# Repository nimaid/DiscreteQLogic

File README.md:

# DiscreteQLogic
My resources and projects relating to digital circuits made out of discrete transistors.

## Efficient Discrete NMOS Logic Gate Designs
I have yet to find a well-compiled source that lists the most efficient NMOS implementations using discrete MOSFETS and resistors. This is likely because, well, it's a very slow and outdated technology that draws more power than CMOS.

However, for DIY projects where one wishes to do the bare minimum of soldering, layout, and purchasing, NMOS provides very good functionality at about half the transistor count of CMOS (at the expense of adding some resistors). Therefore, I have decided to use NMOS for my DIY projects, and as such, I have been collecting the most efficient gate designs, which use fewest transistors and resistors possible.

*(I have been making a library of these parts for both Digital and LTspice, in order to simulate them before building them. You can find these libraries in their respective subfolders of this repository.)*

For this list, I will use some shorthand notation to refer to the total transistor and resistor counts for each part. This shorthand will follow the format `xQyR`, where `x` is the total transistor count and `y` is the total resistor count. So, for example, an XOR gate which was labeled `6Q3R` would require 6 transistors and 3 resistors to build.

Sometimes, you may see the part count listed in the format `(!aQbR/xQyR)`. This means the simplest (lowest part count) version of the part has it's input(s) or output(s) inverted (the `!` means `NOT` or inversion). *This inverted version uses `a` transistors and `b` resistors.* In order to use the part in it's non-inverted state, one or more NOT gates is needed, which increases the total component count per part. *This non-inverted version uses `x` transistors and `y` resistors.* If you are using many of these parts with a shared signal on their inputs (like a clock), it is more economical to invert that signal *once* before it then goes into each of the inverted variants of the part. In addition, sometimes you get inverted outputs for free (like with latches and flip-flops), so you actually don't even need NOT gates a lot of the time! This can save a *TON* of components when building things like multi-bit registers or enablers, where the savings add up with more bits.

Unless otherwise stated, all transistors are N-type.

Resistor values should be chosen based on acceptable power dissipation and speed requirements. If the resistors are large (on the order of 10kΩ+), then power dissipation will be very low (the resistor lets less current through to ground), but the response time of the gate will be much slower. This is due to an inherent weakness in NMOS where it takes longer to charge up the combined gate capacitance of the MOSFETs and the stray capacitance in the wires though a larger resistor. Conversely, smaller values will yield higher power usage, but faster response times.

### NOT (1Q1R)
<details>
<summary>Details</summary>

The simplest gate to construct is a NOT gate (also known as an inverter). This is simply a pullup resistor with a transistor configured to short the output to ground when voltage is applied to it's gate. Make sure you understand how this gate works, because this fundamental principal is the foundation which allows the systematic construction of every other NMOS gate.

</details>

#### This section must be re-written.
<details>
<summary>Show it to me anyway!</summary>

### NAND (2Q1R)
<details>
<summary>Details</summary>

The next step up in complexity is the NAND gate. This is essentially just a NOT gate with an extra transistor in series to ground. This has the effect of only shorting the output to ground if *both* transistors are conducting. This results in the behavior of a NAND gate.

</details>

### NOR (2Q1R)
<details>
<summary>Details</summary>

The NOR gate is almost exactly the same as the NAND gate, except the second transistor is connected in parallel as opposed to series. This has the effect of shorting the output to ground if *either* transistors are conducting. This results in the behavior of a NOR gate.

</details>

### n-way NAND and NOR (\{n\}Q1R)
<details>
<summary>Details</summary>

It is possible to efficiently make NAND and NOR gates that have more than 2 inputs without chaining together the above units. This method uses fewer transistors and resistors than simply chaining the 2-way gates together. We do this be applying the same logic that took us from a 1-way NOT gate to 2-way NAND and NOR gates, but instead of putting only 2 transistors in either series or parallel, we put `n` transistors, where `n` is the number of inputs we want.

Here is an 8-way NAND gate.

Here is an 8-way NOR gate.

</details>

### AND and OR (3Q2R)
<details>
<summary>Details</summary>

The best way to make AND and OR gates happens to be the most straightforward. All we have to do is add a NOT gate after the NAND and NOR gates, as shown.

AND:

OR:

</details>

### AOI[a-b-...] (\{a + b + ...\}Q1R)
<details>
<summary>Details</summary>

The AOI (And-Or-Invert) gate is a bit unusual at first glance, and it is not as well known as the other gates. However, it is essential for building efficient NMOS circuits. This gate acts on "sets" of inputs, and processes them as follows:
- It first runs each "set" of inputs through an `n`-way AND gate, where `n` is the number of inputs in that set.
- The results from all of the AND gates are run through an `m`-way OR gate, where `m` is the number of sets.
- Finally, the output of the OR gate is run through a NOT gate (also called an inverter).

AOI gates are defined by a series of numbers, which specify exactly how many sets of inputs there are, and how many inputs are in each set. Each set can have a different number of inputs, and you can have an many sets as you like. This is in the format `a-b-c-...`, where `a`, `b`, `c`, etc. specify how many inputs each set has, in order. So a `2-3-1` AOI gate would have 3 sets with 2 inputs going to the first AND gate, 3 inputs going to the second AND gate, and the third set has only 1 input that goes directly to the OR gate stage (because AND only makes sense with 2 or more inputs).

Here is an example of an AOI2-2 gate using conventional combinational logic.

So why do we care about this odd gate as a single unit? Why don't we just use combinations of AND and NOR gates whenever we need to do these types of operations? The answer is that all of these logical operations can be easily implemented in a single NMOS logic block that uses far fewer transistors and resistors to achieve the same behavior.

Here is that same AIO2-2 gate in NMOS logic, using 4Q1R.

The way this works is actually very clever. First, observe that this is still arranged with a pullup resistor and transistors that, with some combinations of inputs, shorts to ground. This is the same idea as the NOT gate, and this is where the "inversion" comes from.

Second, observe that there are 2 parallel paths to ground, just like the NOR gate. The only difference is that instead of a single transistor, each path has 2 transistors in series, which is exactly the same method used to construct the NAND gate. Indeed, when either set of series transistors is conducting, the output will be shorted to ground, providing the AND functionality for each set.

Finally, observe that because the sets of series transistors are in parallel with each other, the compound effect of ORing the results of the 2 AND operations is realized.

Here is an example of a 2-1 AOI gate.

And just to make sure it makes sense, here is a 2-2-2-2 AOI gate.

As you can see, you can customize the number of sets and their respective input count to fit your specific needs in the same way you can customize the number of inputs to a NAND or NOR gate.

The final transistor count of each AOI gate will be exactly equal to the total number of inputs, and each AOI gate will only ever use a single resistor.

</details>

### XOR (6Q3R)
<details>
<summary>Details</summary>

It is possible to use an AOI2-2 gate and 2 NOT gates to make an extremely elegant XOR gate, as shown below.

To understand why this works, think about the AOI gate as "a gate that will set it's output to 0 only when a set of inputs is all 1". In this way, we can analyze the truth table of the XOR gate to find which input conditions result in a 0 and test for them with sets of AND gates that have their inputs set to 1 in those conditions.

XOR gate truth table:
```
┌───┬───┬─────┐
│ A │ B │ Out │
╞═══╪═══╪═════╡
│ 0 │ 0 │  0  │
├───┼───┼─────┤
│ 0 │ 1 │  1  │
├───┼───┼─────┤
│ 1 │ 0 │  1  │
├───┼───┼─────┤
│ 1 │ 1 │  0  │
└───┴───┴─────┘
```

We can see that the output is only 0 when both inputs are the same. Therefore, the first AND gate in the AOI2-2 is fed with both inputs directly, so that the output will go to 0 when both inputs are 1. Next, we need the output to also be 0 when both inputs are 0, and we can do this by simply inverting both inputs before feeding them into the second AND gate. Now we have a gate that outputs 0 when the inputs are either both 1 or both 0, and outputs 1 otherwise. This is an XOR gate!

</details>

### XNOR (6Q3R)
<details>
<summary>Details</summary>

We can implement the XNOR gate without using the classic XOR + NOT gate setup. To do so, we simply re-order the NOT gates in our XOR gate design so that the output goes to 0 in each case where the inputs are different, as opposed to the same.

</details>

### Enabler / 3-State Driver (!5Q1R/6Q2R)
<details>
<summary>Details</summary>

This component is a bit unique, as it is the only one which *requires* a few P-channel MOSFETs in addition to N-channel ones. This circuit takes 2 inputs, `In` (input) and `en` (enable). When `en` is 1, the output is equal to `In`. However, when `en` is 0, the output is in a state known as "high impedance". This is a state that is neither a 0 (ground) or 1 (VCC), but instead the output is electrically disconnected entirely.

This is extremely useful when you want to have 2 signals occupy the same wire at different times (the most common example being a data bus inside a computer). To understand the reason why we need a special part for this, lets take an example case where we connect the outputs of 2 AND gates to each other directly. If the first was outputting 1 (VCC) and the second was outputting 0 (ground), then there would be a short-circuit through that wire and those 2 AND gates, which would cause the device to malfunction and likely sustain damage. By putting enablers between the outputs and their shared wire, and by *only enabling a single output at a time*, you can avoid such a disaster.

Before showing you the enabler circuit, it will be useful to first understand how a CMOS-based NOT gate works:

The top transistor is P-channel, and the bottom one is N-channel. In the configuration shown, the N-channel MOSFET will conduct (to ground) when VCC (1) is applied to it's gate, and will act like an open switch when it is grounded (0). This works just like in the N-channel NOT gate. However, the P-channel MOSFET behaves in exactly the opposite way. When VCC (1) is applied to it's gate, it acts like an open switch, and it conducts (to VCC) when the gate is grounded (0).

With this understanding, we can see that when `In` is 0, the upper P-channel MOSFET will be conducting to VCC (1), and the lower N-channel MOSFET will be disconnected, resulting in `Out` being only connected to VCC, and therefore a 1. Conversely, when `In` is 1, the P-channel MOSFET will be open and the N-channel one will be conducting to ground, therefore resulting in a 0. This is the fundamental idea behind CMOS, and it is used in the construction of the enabler circuit.

Now, we are ready to look at the *inverted* enabler circuit (5Q1R):

The top 2 transistors are P-channel, while the lower two are N-channel. *(This means the circuit uses 3 N-channel MOSFETs and 2 P-channel MOSFETs.)*

First, note how to topmost (P-channel) and bottommost (N-channel) MOSFETs both have their gates connected directly to `In`, just like the CMOS NOT gate. This means that if those other 2 MOSFETs weren't in the way, this circuit would actually *be* a CMOS NOT gate, and would therefore just invert the input signal. (Out = !In) Alone this isn't very special, but those 2 MOSFETs in the middle which seperate these ones from `Out` are what actually make this circuit useful as an enabler.

Those 2 middle MOSFETs are also a P-channel/N-channel pair, but with a single critical change from the CMOS NOT gate. Instead of both of their gates being directly connected, the upper-middle P-channel MOSFET has it's gate input inverted by a NOT gate. This means that when `en` is 1, *both* MOSFETs will conduct, but when `In` is 0, *neither* MOSFET will conduct (both act like an open switch). This means that when `en` is 1, the effect of the topmost and bottommost MOSFETs are uninterrupted and `Out` is equal to `!In`. However, when `en` is 0, `Out` is completely disconnected from both VCC and ground, *regardless* of the state of topmost and bottommost MOSFETs. This results in the desired behavior of an enabler, but with the input inverted.

In situations where an inverted input signal is already available without adding a NOT gate (like the inverted output on a latch or flip-flop), you can simply use this inverted version of the enabler and remove a few components from the design. However, there are often times where you can' get away with that, and absolutely need an enabler with a non-inverted input. In these situations, you have to bite the bullet and add a NOT gate, as shown below.

Non-inverted Enabler (6Q2R):

</details>

### Multiplexer (!5Q2R/6Q3R) [WIP] 
<details>
<summary>Details</summary>

[TODO: Explain the MUX API and why it is useful for routing signals.]

This functionality can be accomplished with the following combinational logic:

[TODO: Explain how the AND gates only allow the respective `In` signal through if the other input to the AND gate is on. Explain that because of the NOT gate, only 1 of the AND gates will allow it's signal to pass to the OR gate, effectively discarding the signal not selected by `sel`. Note how because only 1 signal is let through, the output of the OR gate will be equal to the selected signal, which is the desired behavior.]

Here is an efficient implementation of a multiplexer *with an inverted output* using an AOI2-2 gate (5Q2R):

Note that the AOI2-2 gate is almost exactly what we nee to replace the 2 AND gates and 1 OR gate. The only issue is that the output of the OR gate is inverted. Sometimes you can leverage the inverting nature of this circuit to avoid using a NOT gate to invert the inputs/output. However, if you need a non-inverting multiplexer, you must use a NOT gate on the output, as shown (6Q3R):

</details>

### Demultiplexer (!5Q3R/6Q4R) [WIP]
<details>
<summary>Details</summary>

[TODO]

[TODO]

[TODO]

</details>

### RS Latch and SR Latch (4Q2R) [WIP]
<details>
<summary>Details</summary>

The RS latch is the basic form of memory. [TODO: Add API definition and explain why it's useful.]

RS Latch Diagram:

[TODO: Add a breakdown of why it works, step-by step. Also explain metastable (invalid) configurations. Also explain that the circuit starts up in a "random" state.]

Here is the RS latch in the logic simulator, using our NMOS components:

The SR latch is very similar to the RS latch, but it is made of NAND gates instead of NOR gates. In addition, it's inputs are both inverted (active low) and flipped (set on top and reset on bottom). [TODO: Add full API definition and explain why it's useful, especially compared to the RS latch. Note now the inverted inputs are actually useful later on.]

SR Latch Diagram:

[TODO: Add a step-by-step breakdown that references the RS latch breakdown. Explain that this also starts up in a "random" state.]

Here is the SR latch in the logic simulator, using our NMOS components:

</details>

### Multi-Input SR Latch [a-b-...] (\{2 + a + b + ...\}Q2R) [WIP]
<details>
<summary>Details</summary>

[TODO: Introduce the concept of a multi-input SR latch, and explain how it could be useful to have 2 signals as input for `!s` and/or `!r`. Explain the numbering convention briefly, saying it is just like the AOI gate. Also explain how to calculate the transistor count.]

Here is a 2-2 SR latch (6Q2R):

And here is a 1-2 SR latch (5Q2R):

</details>

### Asynchronous D Flip-Flop (!18Q6R/20Q8R) [WIP]
<details>
<summary>Details</summary>

[TODO: Explain the DFF API, and why it is so useful and fundamental to digital design. Introduce the clock and quantized time. Emphasize that the DFF will only switch state once per clock cycle (on the rising edge), and that it will *only* update it's state at the moment of the next rising edge of the clock. Explain that this behavior is deceptively complex to implement.]

[TODO: Explain that to make a DFF, we will have to start from simple building blocks and build on that to solve specific issues with the circuit. Explain that the SR latch winds up being more useful here than the RS, and that the reader will see why soon.]

[TODO: Explain that to start, we need to control an SR latch with an enable signal. Explain the difference between transparent and opaque latches, and how opaque latches are useful as memory devices. Introduce the gated SR latch.]

[TODO: Explain that in order to store a data bit coming in, we need to send exactly opposite signals to `!s` and `!r`. Explain that a NOT gate does this, and the result is called a gated D latch.]

[TODO: Explain that while enable is high, then the output will always be allowed to change with the input. Explain that this can cause issues with oscillation (racing) inside of complex logic circuits like counters. Explain what an edge-triggered device is, and why this solves the problem of racing. Introduce the basic D flip-flop.]

[TODO: Explain how the 2 new SR latches replace the 2 NAND gates on the `!s` and `!r` inputs, and how this makes it edge-triggered instead of a simple opaque latch. Also explain how the lower left NAND gate effectively replaces the NOT gate in the gated D latch.]

[TODO: Explain that because the SR latches start up in an undefined state, we need some way to reliably set and reset the flop-flops manually. Explain that by adding more inputs to the NAND gates allows us to do this, and introduce the final asynchronous DFF.]

[TODO: Explain how the set and reset inputs work, and that they are inverted.]

Here is the equivalent circuit in the logic simulator, using our NMOS components (18Q6R):

If you need a DFF that has non-inverted set and reset inputs, you will need to add NOT gates as shown (20Q8R):

</details>

### Reset-Only D Flip-Flop (!16Q6R/17Q7R)
<details>
<summary>Details</summary>

Often, you don't need to be able to preset a DFF asynchronously. Often, you only need to reset it once when the circuit starts up, and you always want it to be reset to 0. In this case, you can replace a few 3-way NAND gates with 2-way ones, thereby saving some components.

Here is the schematic for such a DFF (16Q6R):

As with the fully asynchronous DFF, the reset input is inverted. To get a non-inverted reset input, use a NOT gate (17Q7R):

</details>

### WIP

</details>

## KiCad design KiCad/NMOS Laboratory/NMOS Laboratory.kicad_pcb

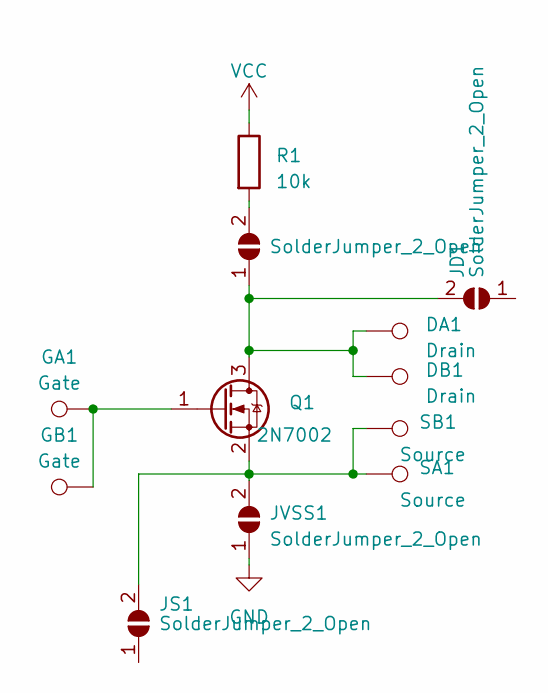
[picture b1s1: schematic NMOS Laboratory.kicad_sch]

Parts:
DA1: Drain; TestPoint_THTPad_D1.5mm_Drill0.7mm
DB1: Drain; TestPoint_THTPad_D1.5mm_Drill0.7mm
GA1: Gate; TestPoint_THTPad_D1.5mm_Drill0.7mm
GB1: Gate; TestPoint_THTPad_D1.5mm_Drill0.7mm
JD1: SolderJumper_2_Open; SolderJumper-2_P1.3mm_Open_TrianglePad1.0x1.5mm
JS1: SolderJumper_2_Open; SolderJumper-2_P1.3mm_Open_TrianglePad1.0x1.5mm
JVCC1: SolderJumper_2_Open; SolderJumper-2_P1.3mm_Open_TrianglePad1.0x1.5mm
JVSS1: SolderJumper_2_Open; SolderJumper-2_P1.3mm_Open_TrianglePad1.0x1.5mm
Q1: 2N7002; SOT-23
R1: 10k; R_0603_1608Metric_Pad0.98x0.95mm_HandSolder
SA1: Source; TestPoint_THTPad_D1.5mm_Drill0.7mm
SB1: Source; TestPoint_THTPad_D1.5mm_Drill0.7mm

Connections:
GND: JVSS1.1 (A)
unnamed: DA1.1, DB1.1, JD1.2 (B), JVCC1.1 (A), Q1.3 (D)
unnamed: JS1.2 (B), JVSS1.2 (B), Q1.2 (S), SA1.1, SB1.1
unnamed: JVCC1.2 (B), R1.2
unnamed: GA1.1, GB1.1, Q1.1 (G)
VCC: R1.1

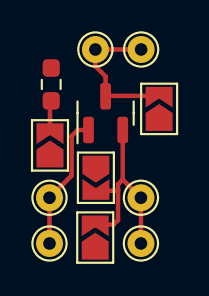
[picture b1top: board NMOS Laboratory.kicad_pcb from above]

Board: 2 copper layers, 12 parts (0 on the bottom side), 4 nets.

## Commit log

2023-04-15 Add initial NMOS components
2023-04-15 refactor
2023-04-15 Added RAM to toy
2023-04-16 Added ROM and PC
2023-04-16 Goodbye pretty 4-nand XOR, here's a better NMOS one with 6Q 3R
    The symmetrical 4 nand gate "diamond" took 8Q 4R, so we save 2Q and 1R.
2023-04-16 Cleaned up XOR (it was using an AOI2-2 lol)
2023-04-16 Optimized "zero" control bit for ALU inputs
2023-04-16 Counter upgrades
2023-04-16 Made a counter toy design to do a full proof of concept with
2023-04-17 Started LTspice sims
2023-04-17 Got first gate working
2023-04-17 Added clock
2023-04-17 NAND
2023-04-17 Added AOI2x2, XOR
2023-04-17 XNOR
2023-04-17 OR gate
2023-04-17 AND gate
2023-04-17 Cleaned up parts
2023-04-17 Add enabler
2023-04-17 Updated enable symbol
2023-04-17 Cleaned up component layouts
2023-04-17 Added pictures for NMOS basics
2023-04-17 Started work on readme
2023-04-17 AOI gates
2023-04-17 Updated mux
2023-04-18 Demultiplexer
2023-04-18 Made names lowercase
2023-04-18 Fixed file names
2023-04-18 Fixed uppercase filenames
2023-04-18 Started work on Eagle design blocks
2023-04-18 Moe design blocks
2023-04-19 Made DFF and byte more compact
2023-04-19 Much better enabler
2023-04-19 Optimized enabler with inversion
2023-04-19 Inverted enabler
2023-04-19 Made a button input and a multiplexer
2023-04-19 Trying comparator, failing
2023-04-19 Added button input with hysteresis
2023-04-19 Gave in and used a read schmitt trigger on my buttons
2023-04-20 Optimized reset and mux with inversions
    No single not gates
2023-04-20 Better DFF
2023-04-20 Simpler architecture that uses ALU to inc PC
2023-04-20 Simplified DFF to JK-based
2023-04-20 TFF (with race...)
    Computers are hard...
2023-04-20 Placeholder TFF and a PC
2023-04-20 DFF revert
2023-04-20 Generalized DFF
2023-04-20 THOSE WERE BAD DFFs!
    TFF is also now DFF based to prevent race.
2023-04-20 Removed outdated images
2023-04-20 Fixed name
2023-04-20 SO MUCH GOOD INFO
2023-04-20 Helpful diagrams for deconstructing the DFF
2023-04-20 Made syn. version of counter, no ripple.
    More stable for use as a PC, but more transistors.
2023-04-21 Fixed AOI naming
2023-04-21 Cleaned up inverted enabler
2023-04-21 Made DFFs modular (from SR latches)
2023-04-21 Updates SR to have both NAND and NOR versions.
2023-04-21 OH, named RS and SR, silly me
2023-04-21 Start work on latches
2023-04-21 Fixed naming
    I remembered to use `git mv` to avoid the end of the world! :D
2023-04-21 First version of latches / DFF
2023-04-21 Added reset-only DFF
2023-04-21 Start MUX and DMUX
2023-04-21 Fixed mux/dmux
2023-04-21 better mux
2023-04-21 Simplified ALU, added conditional decoder
2023-04-23 Testing open collector setup
2023-04-23 Update packages
2023-04-23 A 6x12 grid fits
2023-04-23 Removed useless jumpers
2023-04-23 Added 6x buttons with debouncing
2023-04-23 Added basic power and stripboard
2023-04-23 Added switches, preemptive first version
2023-04-24 Made crossing wires cleaner
2023-04-24 Made simple 4-bit counter that can fit on the 72-transistor lab board
2023-04-24 Added amazing protoboard area.
    https://www.eevblog.com/forum/manufacture/improved-protoboardperfboard-for-direct-soic-mounting/
2023-04-25 Drastically lowered part count
    * D-latches instead of edge-triggered flip-flops
    * Common pulldown open drain enablers
2023-04-25 Start rework on experimenter
2023-04-25 Removed LED
2023-04-25 Create LED output
2023-04-25 Fixed duplicate names?
2023-04-25 Wow, 92 transistors and 8 LEDs
2023-04-25 Better power distribution
2023-04-25 Fixed power input connector
2023-04-25 Added startup circuit!
    Not so bad lol, who needs reset lines?
2023-04-25 Simplified startup circuit
2023-04-25 Lots of changes
2023-04-27 ALU simplifications, proper PC
2023-04-27 Simplifiied experiment board
2023-04-27 Started emulator with the FET-80 ALU
2023-04-27 Eagle v1 done
2023-04-27 Started attempt to make board in KiCad
2023-04-28 Better multiplexer, used pre-inverted output
2023-04-28 Simplified PC by sharing NOT gate on D input to TFF
2023-04-28 NMOS-based schmitt inverter
2023-04-28 Simplified XNOR with OAI gate, made inverted inverter with it
2023-04-28 Realised the input/output inverters could be replaced with NAND and multiple cycles, lol
    This went from the HACK ALU to almost the MyNOR "ALU". Just an adder, an 8 channel NAND gate, and a multiplexer! The NAND is a free additional output from the adder, too! (It also has AND and XOR out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
2023-04-28 Added schmitt inverter to LTspice
2023-04-29 Wow, a full adder gives free XOR, AND. NAND, and NOR
    How generous. I call it an Adder+, and it plus a multiplexer is my ALU now.
2023-04-29 Started work on first abstract implimentation of the machine code
2023-04-30 Added registers RAM to the emulator
2023-04-30 Copied some of my work from NAND2Tetris for the parser
2023-04-30 Symbol parsing
2023-04-30 Finished symbol extracting
2023-04-30 Finished basic assembly parser
2023-04-30 Almost done with the assembler.
2023-04-30 Basic symbolic assembler done
2023-04-30 Using @ to denote implicit use of MEM
2023-04-30 UPPER
2023-04-30 Allowed MEM to access non-direct values
2023-04-30 Indirect memory addressing works
2023-04-30 Finished program ROM
2023-04-30 Fixed direct values in dest
2023-04-30 Added multi-level pointers
2023-04-30 Added way to view preprocessed assembly
2023-04-30 Remapped IO to be more efficient
2023-04-30 Refactored to separate files
2023-04-30 Better practices when programming pointers
2023-04-30 better formatting
2023-04-30 Added class for FET-80 system
2023-04-30 Added required methods to FET-80
2023-04-30 spacing
2023-04-30 Generalized symbol table constants
2023-04-30 Rename file extension
2023-04-30 More parameter generalizations
2023-04-30 Begin Emulator class
2023-04-30 Added basic emulation!
2023-04-30 Cleaned up structure of assembler
2023-04-30 Fixed bug in assembly code!
    I know it's a bug because MY EMULATOR WORKS!
2023-04-30 Added human-readable assembly methods
2023-04-30 Start work on TKinter GIU
2023-05-01 Transfer FET-80 stuff to new repo
2023-05-02 101 transistors for a hex decoder!
2023-05-03 Did the math, got the 7-segment hex decoder to 88Q
2023-05-03 Yup, 88Q. And now I have mastered NMOS boolean expressions.
2023-05-03 Started experiments with sub-gate level design optimizations
2023-05-04 Started restructuring Digital circuits
2023-05-04 Rename and multiple NAND/NOT/NOR
2023-05-04 SR and RS latches
2023-05-04 Added gated D latch
    Using fancy compound NAND circuits
2023-05-04 Better D latch for NMOS
2023-05-04 Renamed minimal SR latch
2023-05-04 Added DFF and TFF variants
    1 transistor can pull the reset lines down. I made versions with integrated pull-downs for each flop, and ones with the pull-downs missing for use with a single shared pull-down.
2023-05-04 Made pd mean "Has pull-down transistor on set/reset line"
2023-05-04 That isn't a viable method sadly, logic oscillates
2023-05-04 Added Schmitt trigger inverter (does not work in Digital)
2023-05-05 Binary Clock
2023-05-05 Updated sexagesimal clock
2023-05-05 Made better sexagesimal versions with color coded LEDs
2023-05-05 Started work on BCD clock
2023-05-05 Mock-up of colored light idea
2023-05-05 Much nicer layout
    I'm probably gonna use the H:M:S one, because a 1 Hz signal is a simple CD4060, 32.768 kHz crystal, and a basic 13Q6R TFF away. Plus, more blinkenlights.
2023-05-05 Added DFF to LTspice
2023-05-05 Renamed LTspice models
2023-05-05 Resettable DFF
2023-05-05 Moved images and documents around
2023-05-12 Simplified input AND reduced transistors
2023-05-12 Clock generator module
2023-05-19 kicad start
2023-05-19 op amp clock
2023-05-19 Started clock simulator
2023-05-22 Holy shit, I opened my third eye and halved the transistors (187)
2023-05-22 Okay, that broke my sim
2023-05-22 Okay, these work in my sim
2023-05-22 More optimizations
2023-05-22 Better layout
2023-05-22 New pictures
